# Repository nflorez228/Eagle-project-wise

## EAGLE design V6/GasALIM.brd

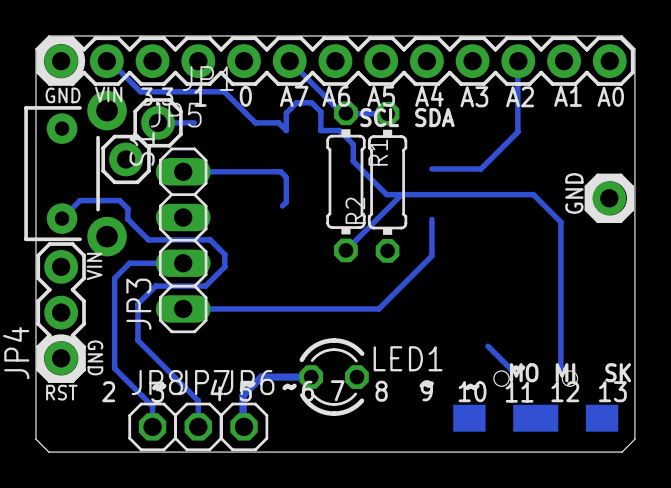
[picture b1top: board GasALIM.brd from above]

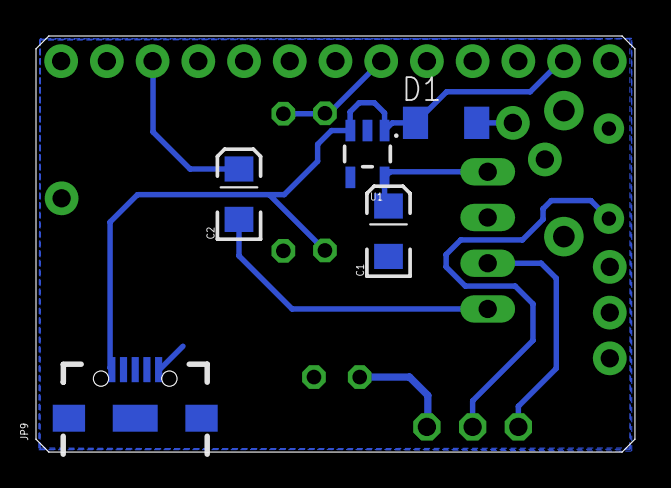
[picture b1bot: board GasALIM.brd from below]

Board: 2 copper layers, 33.3 x 23.1 mm, 18 parts (5 on the bottom side), 11 nets.

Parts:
ANALOGSIDE: M13; 1X13
C1, C2: 10uF; EIA3216
D1: MELF-MLL34
JP1, JP2, JP5: M01PTH; 1X01
JP3: 1X04
JP4: 1X03
JP6, JP7, JP8: 1X01
JP9: Micro USB; USB-AB-MICRO-SMD_V03
LED1: LED3MM
R1, R2: 0204/7
S1: SWITCH-MOMENTARY-2SIDE_EZ; TACTILE-PTH-SIDEEZ
U1: SOT23-5@1

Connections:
GND: ANALOGSIDE.13, C1.C, JP3.3, JP5.1, R2.1, S1.1, U1.2
GND1: JP2.1, JP9.GND1, LED1.K
unnamed: JP7.1, S1.2
unnamed: JP3.2, JP8.1
unnamed: C2.C, JP3.1
unnamed: ANALOGSIDE.3, C2.A
unnamed: ANALOGSIDE.8, R1.1, R2.2
unnamed: JP6.1, LED1.A
unnamed: D1.2, JP1.1
unnamed: C1.A, JP3.4, U1.5
VIN: ANALOGSIDE.12, D1.1, JP9.VBUS1, R1.2, U1.1, U1.3

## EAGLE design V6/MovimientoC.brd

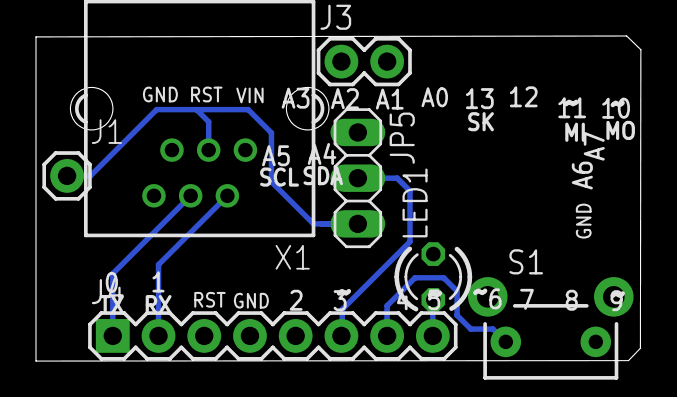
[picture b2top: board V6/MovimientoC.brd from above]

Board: 2 copper layers, 33.6 x 18.1 mm, 7 parts (0 on the bottom side), 7 nets.

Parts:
J1: 1X01
J3: 1X02
J4: 1X08
JP5: 1X03
LED1: LED3MM
S1: SWITCH-MOMENTARY-2SIDE_EZ; TACTILE-PTH-SIDEEZ
X1: YH-55-10

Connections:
GND: J4.4, LED1.K, S1.2, X1.5
unnamed: J4.7, S1.1
unnamed: J4.8, LED1.A
unnamed: J1.1, JP5.3, X1.3
unnamed: J4.2, X1.2
unnamed: J4.6, JP5.2
VIN: J4.1, X1.4

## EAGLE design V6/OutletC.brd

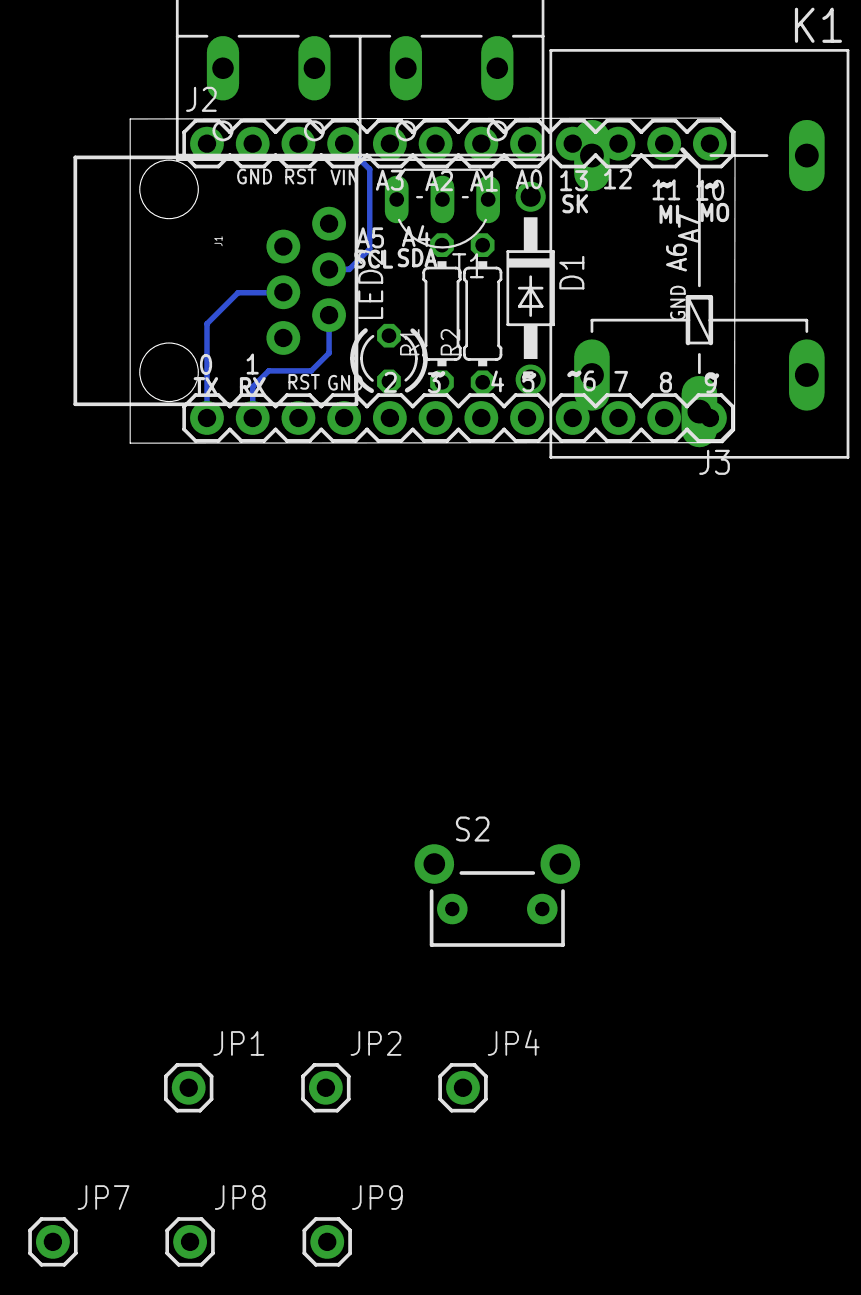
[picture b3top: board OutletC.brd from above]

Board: 2 copper layers, 33.6 x 18.1 mm, 17 parts (0 on the bottom side), 13 nets.

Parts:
D1: 1N4004; DO41-10
J1: RJ11; RJ11-6
J2, J3: 1X12
JP1, JP2, JP4, JP7, JP8, JP9: M01PTH; 1X01
K1: G5L; G5LE
LED2: LED3MM
R1, R2: 0204/7
S2: SWITCH-MOMENTARY-2SIDE_EZ; TACTILE-PTH-SIDEEZ
T1: 2SC458; TO92-ECB
X1: Out- In- Out+ In+; W237-4P

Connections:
GND: J1.1, J1.2, J2.2, J3.9, JP2.1, JP8.1, R2.1, S2.1, T1.E
unnamed: J1.4, J3.12
unnamed: J3.6, S2.2
unnamed: J1.5, J3.11
unnamed: R1.2, R2.2, T1.B
unnamed: D1.A, K1.1, T1.C
unnamed: D1.C, JP1.1, JP9.1, K1.2
unnamed: J3.5, R1.1
unnamed: J3.7, LED2.A
unnamed: JP7.1, X1.2, X1.3
unnamed: K1.S, X1.1
unnamed: JP4.1, K1.P, X1.4
VIN: J1.3, J2.4

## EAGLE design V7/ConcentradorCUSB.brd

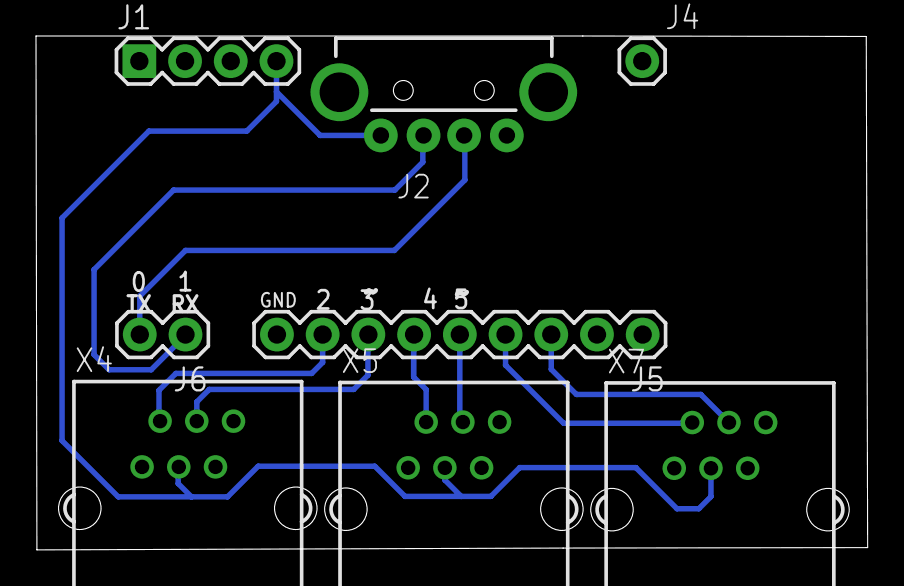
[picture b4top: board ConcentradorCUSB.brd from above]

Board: 2 copper layers, 46.2 x 28.5 mm, 8 parts (0 on the bottom side), 10 nets.

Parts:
J1: 1X04
J2: USB-A-H
J4: 1X01
J5: 1X09
J6: 1X02
X4, X5, X7: YH-55-10

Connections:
GND: J1.2, J2.GND, J5.9, X4.5, X5.5, X7.5
unnamed: J5.5, X5.4
unnamed: J5.6, X5.2
unnamed: J5.3, X7.4
unnamed: J2.D+, J6.2
unnamed: J5.4, X7.2
unnamed: J5.7, X4.4
unnamed: J5.8, X4.2
unnamed: J2.D-, J6.1
VIN: J1.4, J2.VBUS, X4.3, X5.3, X7.3

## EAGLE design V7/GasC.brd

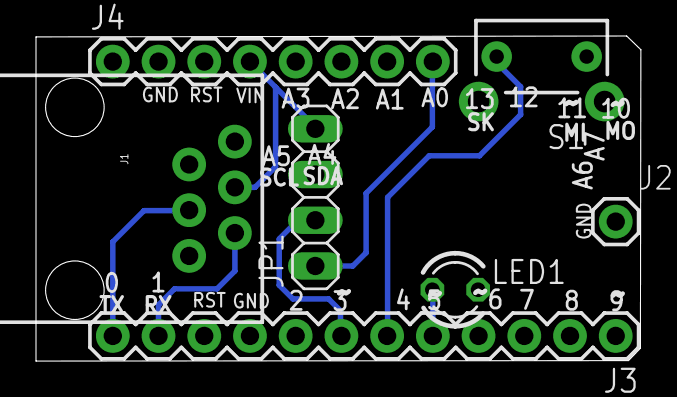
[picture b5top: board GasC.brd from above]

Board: 2 copper layers, 33.6 x 18.1 mm, 7 parts (0 on the bottom side), 9 nets.

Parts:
J1: RJ11; RJ11-6
J2: 1X01
J3: 1X12
J4: 1X08_ROUND
JP1: 1X04
LED1: LED3MM
S1: SWITCH-MOMENTARY-2SIDE_EZ; TACTILE-PTH-SIDEEZ

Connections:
AGND: J2.1, J3.9, LED1.K, S1.1
GND: J1.1, J1.2, J4.2, JP1.3
unnamed: J3.6, S1.2
unnamed: J3.7, JP1.2
unnamed: J3.5, LED1.A
unnamed: J1.4, J3.12
unnamed: J1.5, J3.11
unnamed: J4.8, JP1.1
VIN: J1.3, J4.4, JP1.4

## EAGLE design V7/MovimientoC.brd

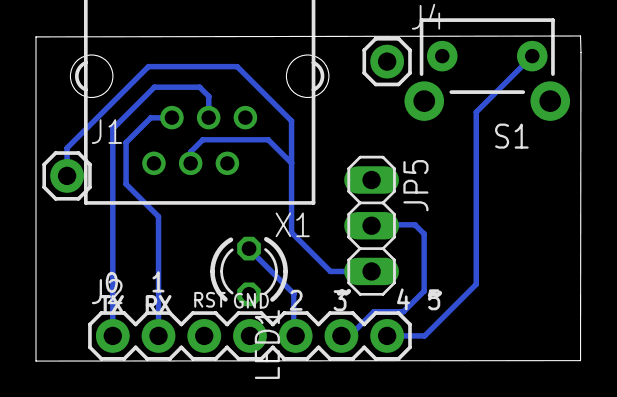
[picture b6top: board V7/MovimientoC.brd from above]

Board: 2 copper layers, 30.3 x 18.1 mm, 7 parts (0 on the bottom side), 7 nets.

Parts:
J1, J4: 1X01
J2: 1X07
JP5: 1X03
LED1: LED3MM
S1: SWITCH-MOMENTARY-2SIDE_EZ; TACTILE-PTH-SIDEEZ
X1: YH-55-10

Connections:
GND: J2.4, LED1.K, S1.2, X1.2
unnamed: J2.7, S1.1
unnamed: J2.5, LED1.A
unnamed: J1.1, JP5.3, X1.4
unnamed: J2.2, X1.5
unnamed: J2.6, JP5.2
VIN: J2.1, X1.3

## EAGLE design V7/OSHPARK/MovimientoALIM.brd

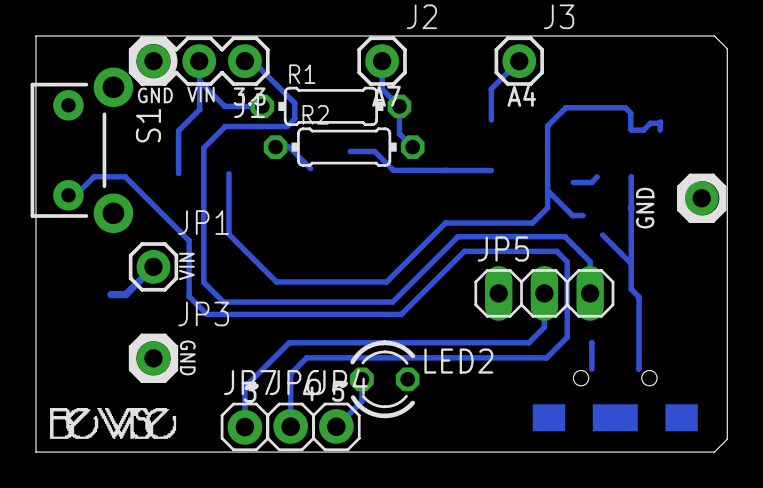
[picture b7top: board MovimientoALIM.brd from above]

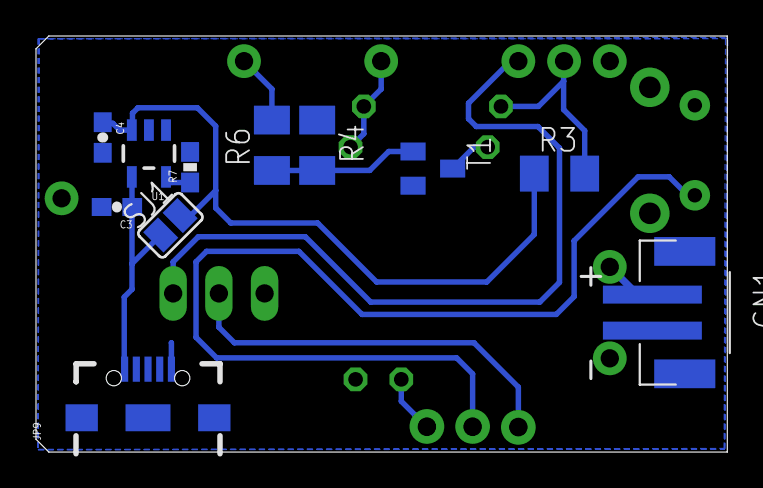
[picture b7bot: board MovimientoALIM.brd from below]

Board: 2 copper layers, 38.4 x 23.1 mm, 25 parts (11 on the bottom side), 16 nets.

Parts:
C3, C4: 4.7uF; 0603-CAP
CN1: JST-PH-2-SMT
J1: 1X03
J2, J3: 1X01
JP1, JP2, JP3, JP4, JP6, JP7: 1X01
JP5: 1X03
JP9: Micro USB; USB-AB-MICRO-SMD_V03
LED2: LED3MM
R1, R2: 0204/7
R3, R4, R6: M1206
R7: 2.0k; 0603-RES
S1: SWITCH-MOMENTARY-2SIDE_EZ; TACTILE-PTH-SIDEEZ
SJ1: SJ
T1: BC850; SOT23
U1: MCP73831; SOT23-5

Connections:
AGND: CN1.2, JP3.1, JP5.1
GND: J1.3, S1.1
GND1: C3.2, C4.2, JP2.1, JP9.GND1, LED2.K, R4.1, R7.2, T1.2, U1.2
unnamed: JP6.1, S1.2
unnamed: JP5.2, JP7.1
unnamed: J3.1, R6.2
unnamed: C3.1, JP9.VBUS1, SJ1.1, U1.4
unnamed: J2.1, R1.2, R2.2
unnamed: R2.1, T1.3
unnamed: R4.2, R6.1, T1.1
unnamed: J1.1, JP5.3
unnamed: C4.1, R3.1, SJ1.2, U1.3
unnamed: JP4.1, LED2.A
unnamed: CN1.1, JP1.1
PROG: R7.1, U1.5
VCC: J1.2, R1.1, R3.2

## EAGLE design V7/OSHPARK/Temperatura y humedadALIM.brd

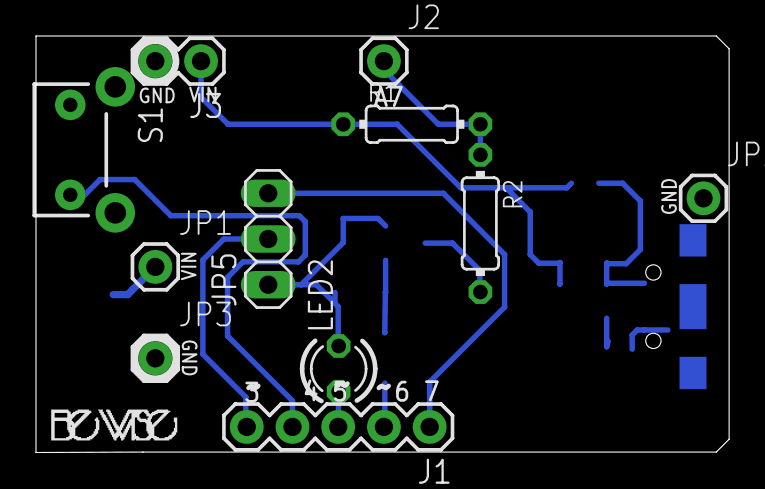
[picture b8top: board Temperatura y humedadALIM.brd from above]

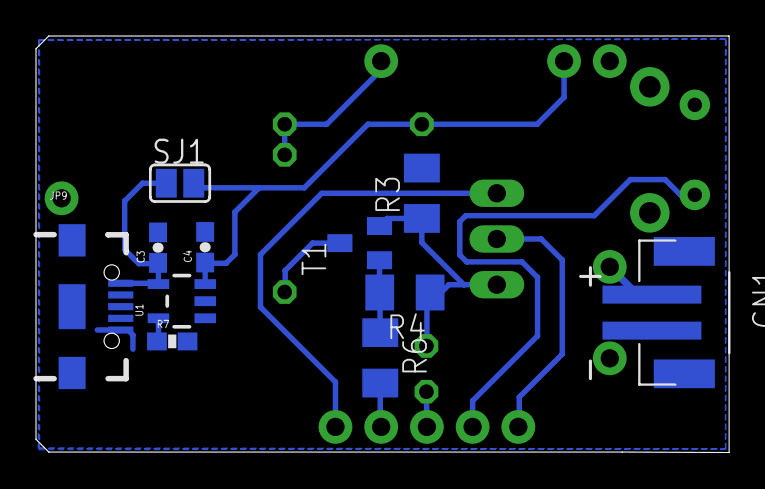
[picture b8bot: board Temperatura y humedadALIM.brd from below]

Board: 2 copper layers, 38.5 x 23.1 mm, 22 parts (11 on the bottom side), 16 nets.

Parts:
C3, C4: 4.7uF; 0603-CAP
CN1: JST-PH-2-SMT
J1: 1X05
J2: 1X01
J3: 1X02
JP1, JP2, JP3: 1X01
JP5: 1X03
JP9: Micro USB; USB-AB-MICRO-SMD_V03
LED2: LED3MM
R1, R2: 0204/7
R3, R4, R6: M1206
R7: 2.0k; 0603-RES
S1: SWITCH-MOMENTARY-2SIDE_EZ; TACTILE-PTH-SIDEEZ
SJ1: SJ
T1: BC850; SOT23
U1: MCP73831; SOT23-5

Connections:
AGND: CN1.2, JP3.1
GND: J3.2, R3.2, S1.1
GND1: C3.2, C4.2, JP2.1, JP9.GND1, R7.2, U1.2
unnamed: J1.4, S1.2
unnamed: J1.5, JP5.2
unnamed: J1.1, JP5.3
unnamed: JP5.1, LED2.K, R3.1, R4.1, T1.2
unnamed: C3.1, JP9.VBUS1, SJ1.1, U1.4
unnamed: J2.1, R1.2, R2.1
unnamed: R2.2, T1.3
unnamed: R4.2, R6.1, T1.1
unnamed: J1.2, R6.2
unnamed: J1.3, LED2.A
PROG: R7.1, U1.5
VCC: CN1.1, JP1.1
VIN: C4.1, J3.1, R1.1, SJ1.2, U1.3

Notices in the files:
parts and their libraries:
SparkFun-Connectors: Licensing: CC v3.0 Share-Alike You are welcome to use this library for commercial purposes.
SparkFun-Electromechanical: Licensing: Creative Commons ShareAlike 4.0 International - https://creativecommons.org/licenses/by-sa/4.0
